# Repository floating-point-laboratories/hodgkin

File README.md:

# Project Hodgkin
Project Hodgkin is an open-source (semi) Arduino Nano compatible microcontroller development board that is developed to IEC 60601 standards for 2xMOPP (methods of patient protection) isolation. It is intended for educational settings to enable students and enthusiasts to safely interface with biopotential amplifier circuits.

**Will this device be IEC 60601 certified / FDA cleared / etc.?**
*Due to the nature of this device's application, which is to enable students to interface with biomedical electronics which they have designed and built themselves, it is not practical to pursue any form of formal medical device certification. This device's performance will depend entirely on the quality of the circuits that it is attached to; it therefore cannot and should not be used as a substitute for any medical device for diagnostic or therapeutic purposes. The intention of this project is to provide a safe interface between these experimental circuits and a computer via USB interface so that users are not exposed to dangerous voltages or currents in the case of PC power supply failure or mains power surge.*

**What do you mean "semi" Arduino Nano compatible?**
*This device is planned to share a pinout, footprint, and firmware with the Arduino Nano V3.0 (based on the ATmega328p microcontroller). However, some changes will be necessary to ensure safe operation of the device while maintaining low cost. These include the inability to draw microcontroller power from the on-board USB port, and incompatibility with shields / expansion boards which are connected to mains power.*

**Why use an optical link? Why not use a wireless connection like BLE?**
*This is something that was certainly considered, but was ultimately abandoned in favor of a direct optical serial link for three primary reasons:*

*1. Cost. The goal for this project is to meet the necessary safety requirements without dramatically adding to the cost of an Arduino Nano. Obviously some added costs are unavoidable, but a full RF solution was deemed an uneccessary cost.*

*2. Stability. Since this project is intended as a direct Aduino Nano substitute for use by students, it was important to us that it behave as similarly to a stock Arduino as possible. This means plug-and-play direct USB-to-serial simplicity whenever possible.*

*3. Security. Athough this device is not intended for use as a medical device, it is built with similar design philosophies in mind. In general, wireless solutions are typically not implemented in medical devices unless there is a compelling reason to do so to avoid potential data leaks / HIPAA violations.*

**When can I purchase this device?**
*This device is planned for inclusion in the electronics kit given to all students enrolled in SBEE 2020. Standalone sale of the device will certainly be considered if there is a demand for it. In the meantime, you are welcome to build one yourself using the files available in this repository.*

## About The Shoulders of Giants
In 1676, Isaac Newton, one of the most influential mathematicians and scientists of all time, famously wrote:

> "If I have seen further, it is by standing on the shoulders of giants."

The Shoulders of Giants, Inc. (TSoG) is a nonprofit (501(c)(3)) organization founded in 2013 on a vision that world-class science education should be available to all students of all ages. Since 2015, The Shoulders of Giants has offered an immersive, ongoing mentorship program for dedicated students who would like the opportunity to study more closely under the guidance of Dr. Steven J. Foland. This program is designed to provide middle and high school students with a broad foundation of knowledge and skills across science and engineering disciplines, experience working and communicating in a professional environment, and helps them develop the study habits necessary to achieve success at the university level and beyond.

In 2019, this world-class program became available to students everywhere with the launch of TSoG.tv. This online platform, created in collaboration between The Shoulders of Giants, Inc. and its sister-company Floating Point Laboratories, LLC, provides at-home exercises, live-streaming, and project support to students anywhere in the world.

## About #SBEE2020
Since 2015, The Shoulders of Giants has offered its flagship summer program, the Summer Biomedical Engineering Experience (SBEE) to high school students interested in exploring careers in biomedical engineering and related medical sciences. The original contents of the program were 60 hours of rigorous curriculum covering biomedical electronics, mechanical CAD and 3D printing, and microcontroller programming. Through this program, nearly 400 students have designed and built their own electromyograph (EMG) controlled prosthetic hands. 

In spring 2019, TSoG co-founder and Floating Point Laboratories managing director Dr. Steven J. Foland [announced an initiative](https://www.youtube.com/watch?v=rmPsDaRs3cc) to develop the SBEE curriculum into a TSoG.tv experience for students around the world in summer 2020. This has become known as the #SBEE2020 initiative. Dr. Foland hosted a successful 24-hour livestream fundraiser on June 29-30th 2019, teaching a prototype SBEE 2020 curriculum in one marathon session which can be viewed [here](https://www.tsogiants.org/2019/07/02/24-hour-challenge-physiological-signals-and-biomedical-electronics/). 

As of August 2019, development for SBEE 2020 is currently underway. In order to best serve the community, several new devices need to be developed to provide safe, affordable access to the technologies necessary for students to explore and interface with human biosignals. Among these are: Project Hodgkin, an inexpensive Arduino compatible microcontroller development board built to follow IEC 60601 safety standards; and Project Huxley, a USB oscilloscope developed with biomedical applications and safety standards in mind.

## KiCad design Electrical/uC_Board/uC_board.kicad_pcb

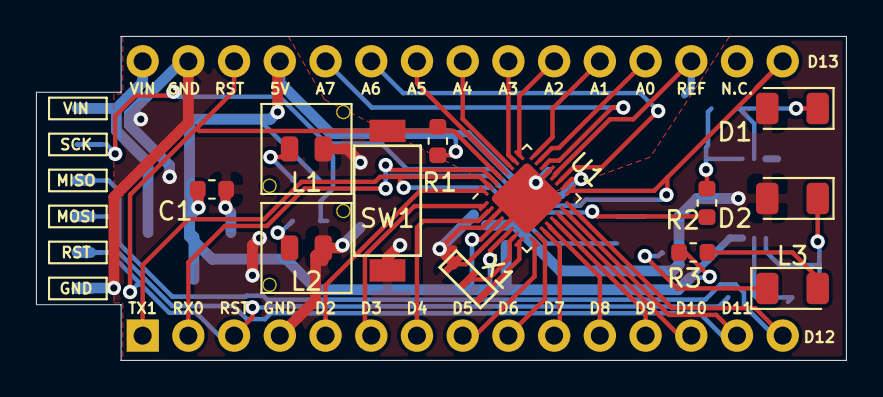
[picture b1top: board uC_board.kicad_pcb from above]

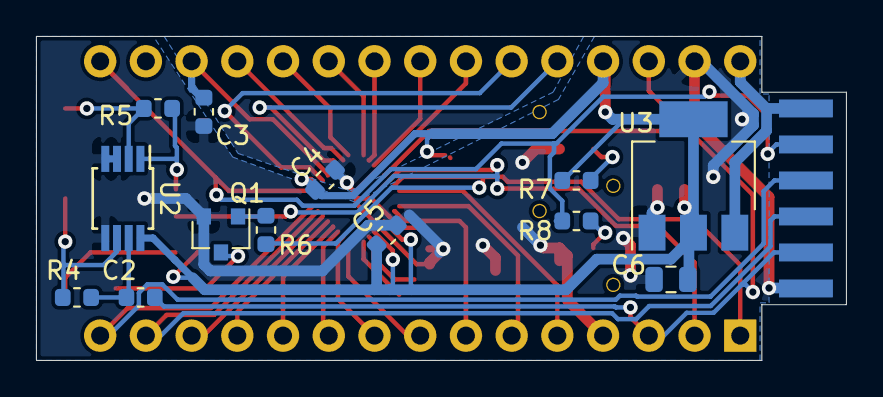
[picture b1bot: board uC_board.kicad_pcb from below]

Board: 2 copper layers, 45.0 x 18.0 mm, 27 parts (14 on the bottom side), 38 nets.

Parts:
C1, C4, C5: 1uF; C_0603_1608Metric
C2, C3: 100nF; C_0603_1608Metric
C6: 4.7uF; C_0805_2012Metric
D1, D2: D_Photo; D_1206_3216Metric
J1: Card Edge Connector; card_edge_6p_single_side
J2: Arduino Breakout Pins; ArdNanoStrip
L1: GREEN; LED_0805_LightPipe_Long
L2: YELLOW; LED_0805_LightPipe_Long
L3: LED; LED_1206_3216Metric
Q1: BC850; SOT-23
R1, R2, R3, R6, R7, R8: 1k; R_0603_1608Metric
R4, R5: 1M; R_0603_1608Metric
SW1: SW_Push; PTS636-G-2.5-NoGND
U1: ATmega328PB-AU; QFN-32-1EP_4x4mm_P0.4mm_EP2.9x2.9mm
U2: OPA2381; MSOP-8_3x3mm_P0.65mm
U3: LM1117MPX-5.0; LM1117
X1: CSTNE16M0V530000R0

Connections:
+5V: C1.1, C4.1, C5.1, C6.1, J2.27, R1.1, R3.2, R7.2, U1.4, U1.6, U1.18, U2.8, U3.2
/A0: J2.19, U1.23
/A1: J2.20, U1.24
/A2: J2.21, U1.25
/A3: J2.22, U1.26
/A4: J2.23, U1.27
/A5: J2.24, U1.28
/A6: J2.25, U1.19
/A7: J2.26, U1.22
/AREF: C3.1, J2.18, U1.20
/D0: J2.2, R2.2, U1.30
/D1: J2.1, R6.2, U1.31
/D2: J2.5, U1.32
/D3: J2.6, U1.1
/D4: J2.7, U1.2
/D5: J2.8, U1.9
/D6: J2.9, U1.10
/D7: J2.10, U1.11
/D8: J2.11, U1.12
/D9: J2.12, U1.13
/D10: J2.13, U1.14
/D11: J1.4, J2.14, U1.15
/D12: J1.3, J2.15, U1.16
/D13: J1.2, J2.16, R8.2, U1.17
/RESET: C2.2, J1.5, J2.3, J2.28, R1.2, SW1.2, U1.29
/RX: R2.1, R5.1, U2.1
/TX: Q1.1, R6.1
GND: C1.2, C3.2, C4.2, C5.2, C6.2, D1.2, D2.2, J1.6, J2.4, J2.29, L1.1, L2.1, Q1.2, SW1.1, U1.3, U1.5, U1.21, U1.33, U2.3, U2.4, U2.5, U3.1, X1.3
unnamed: C2.1, R4.1, U2.7
unnamed: D1.1, R5.2, U2.2
unnamed: D2.1, R4.2, U2.6
unnamed: L1.2, R7.1
unnamed: L2.2, R8.1
unnamed: L3.1, Q1.3
unnamed: L3.2, R3.1
unnamed: U1.7, X1.2
unnamed: U1.8, X1.1
VCC: J1.1, J2.30, U3.3

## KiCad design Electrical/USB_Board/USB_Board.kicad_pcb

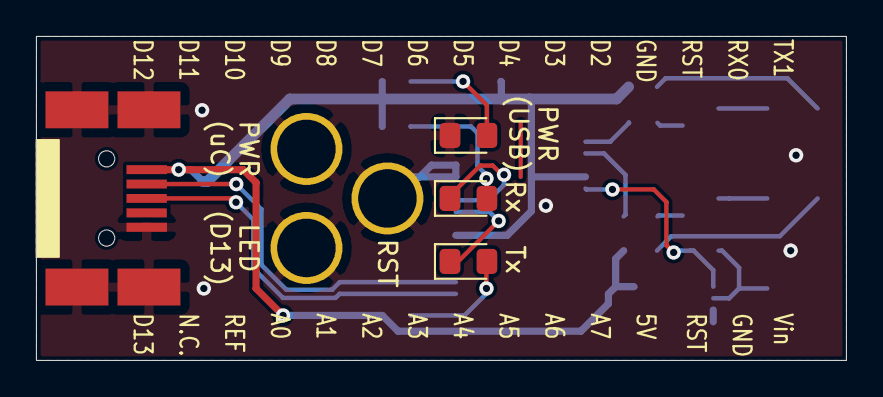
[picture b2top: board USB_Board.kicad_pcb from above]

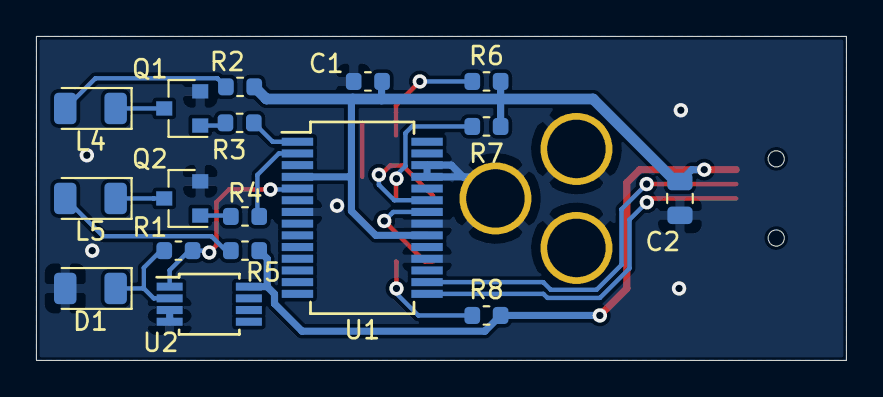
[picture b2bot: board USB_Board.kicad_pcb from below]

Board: 2 copper layers, 45.0 x 18.0 mm, 24 parts (17 on the bottom side), 19 nets.

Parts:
C1: 100 nF; C_0603_1608Metric
C2: 4.7uF; C_0805_2012Metric
D1: PD_RX; D_1206_3216Metric
H1, H2: light_pipe
H3: Switch; light_pipe
J1: USB_B_Mini; Molex_67503-1020
L1: blue; LED_0805_2012Metric_Pad1.15x1.40mm_HandSolder
L2: red; LED_0805_2012Metric_Pad1.15x1.40mm_HandSolder
L3: green; LED_0805_2012Metric_Pad1.15x1.40mm_HandSolder
L4: IR_TX; LED_1206_3216Metric
L5: IR_DTR; LED_1206_3216Metric
Q1, Q2: BC850; SOT-23
R1, R2, R5, R7, R8: R; R_0603_1608Metric
R3, R4: 4.7k; R_0603_1608Metric
R6: R_US; R_0603_1608Metric
U1: FT232RL; SSOP-28_5.3x10.2mm_P0.65mm
U2: OPA2381; MSOP-8_3x3mm_P0.65mm

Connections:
+5V: C1.1, C2.1, J1.1, R2.2, R5.2, R6.2, R7.2, R8.2, U1.4, U1.20, U2.8
/DTR: R4.1, U1.2
GND: C1.2, C2.2, D1.2, H1.1, H2.1, H3.1, J1.5, J1.6, L1.1, Q1.2, Q2.2, U1.7, U1.18, U1.21, U1.25, U1.26, U2.3, U2.4
unnamed: D1.1, R1.2, U2.2
unnamed: J1.2, U1.16
unnamed: J1.3, U1.15
unnamed: L1.2, R6.1
unnamed: L2.1, U1.23
unnamed: L2.2, R7.1
unnamed: L3.1, U1.22
unnamed: L3.2, R8.1
unnamed: L4.1, Q1.3
unnamed: L4.2, R2.1
unnamed: L5.1, Q2.3
unnamed: L5.2, R5.1
unnamed: Q1.1, R3.2
unnamed: Q2.1, R4.2
unnamed: R1.1, U1.5, U2.1
unnamed: R3.1, U1.1

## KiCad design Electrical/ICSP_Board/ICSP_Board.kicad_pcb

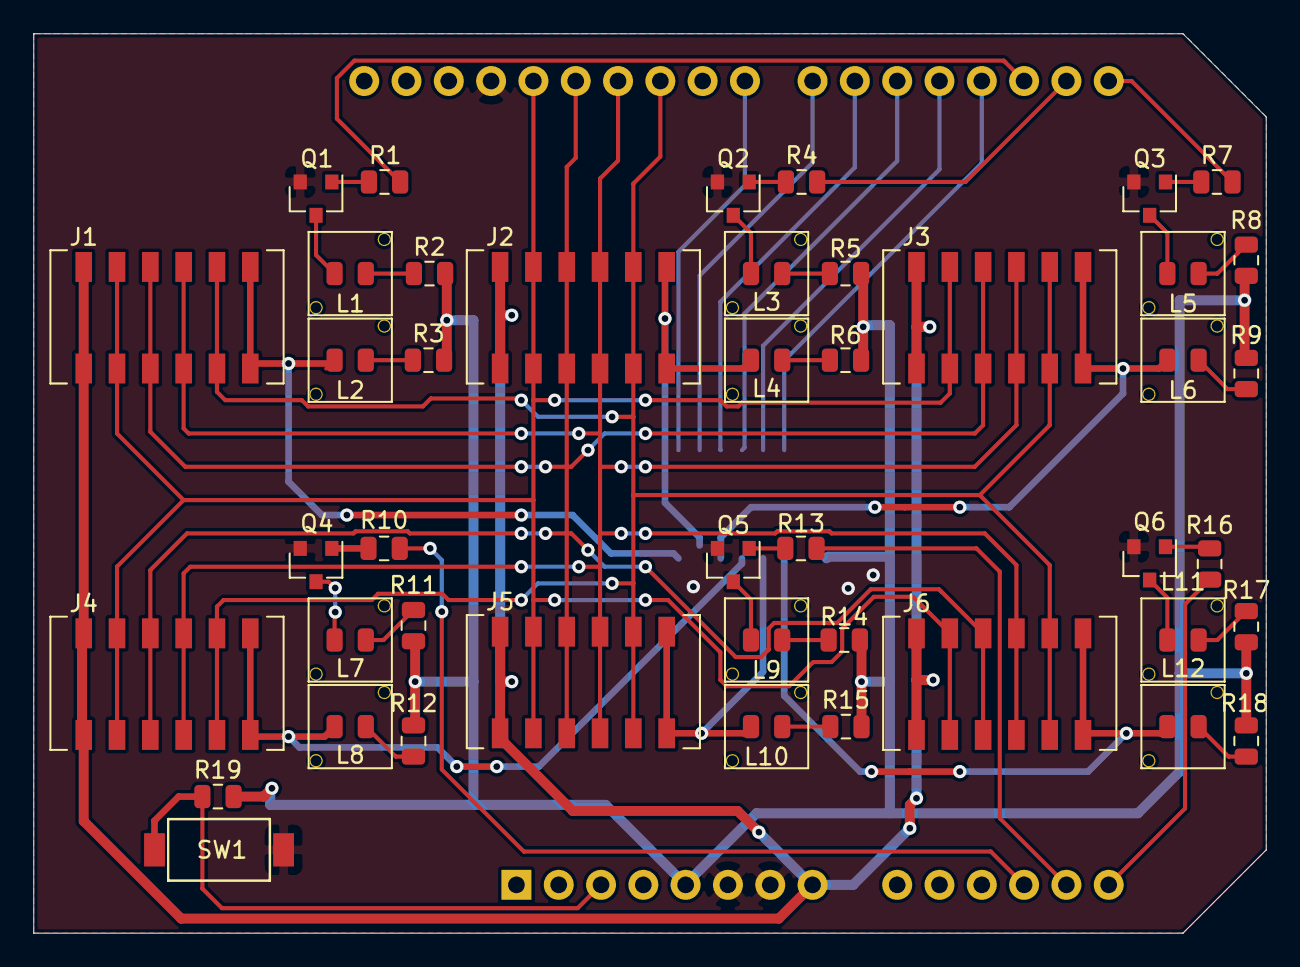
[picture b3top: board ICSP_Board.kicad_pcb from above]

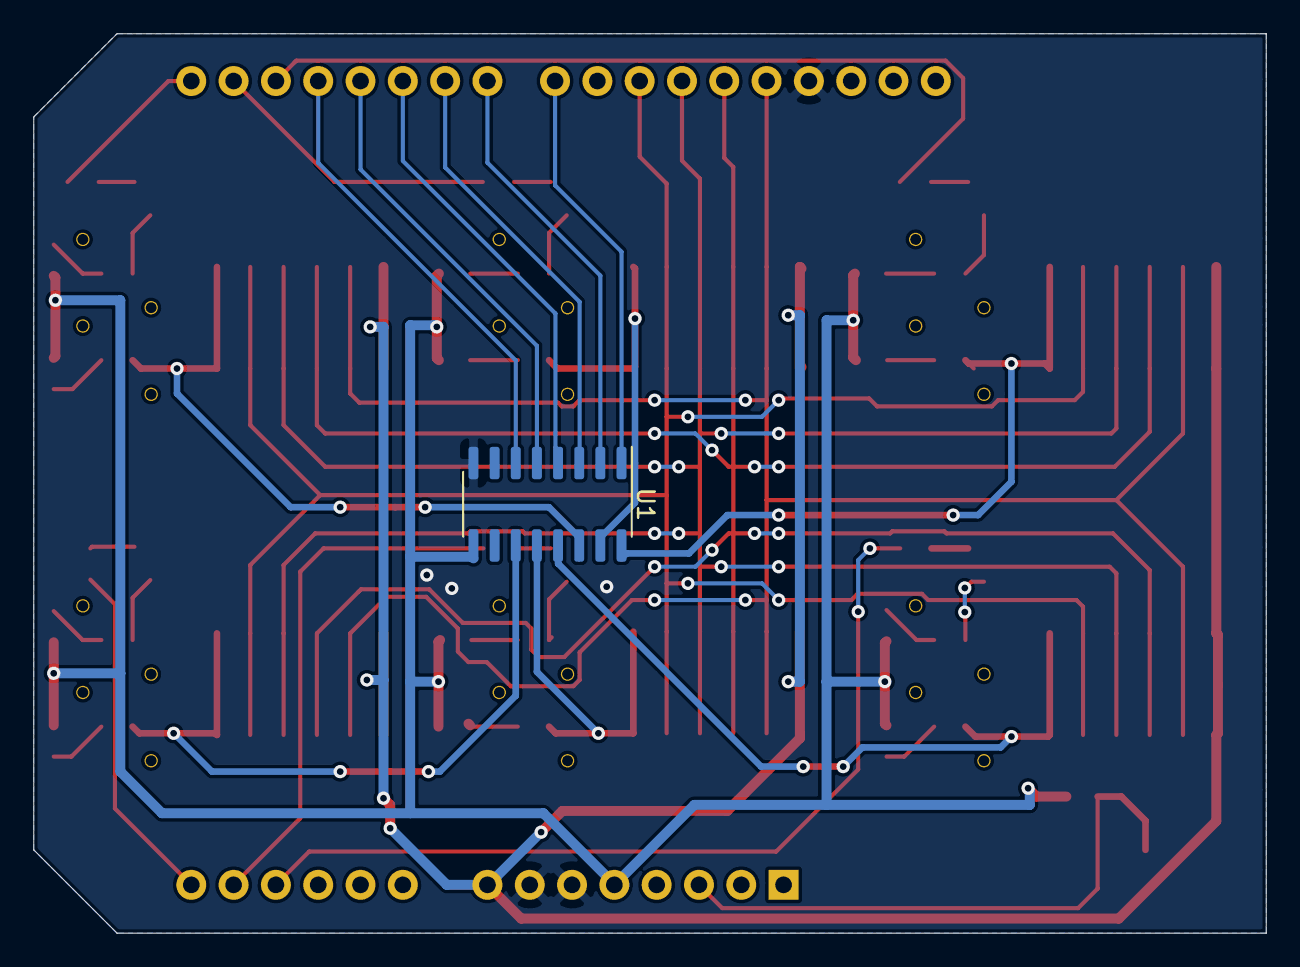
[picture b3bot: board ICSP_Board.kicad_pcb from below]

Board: 2 copper layers, 74.0 x 54.0 mm, 46 parts (2 on the bottom side), 50 nets.

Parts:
A1: Arduino_UNO_R3
J1, J2, J3, J4, J5, J6: AVX 009159006551906; card_edge_6p
L1, L3, L5, L7, L9, L11: gLED; LED_0805_LightPipe
L2, L4, L6, L8, L10, L12: rLED; LED_0805_LightPipe
Q1, Q2, Q3, Q4, Q5, Q6: BC850; SOT-23
R1, R2, R3, R4, R5, R6, R7, R8, R9, R10, R11, R12, R13, R14, R15, R16, R17, R18, R19: R_US; R_0805_2012Metric
SW1: SW_Push; PTS636-G-2.5-NoGND
U1: ULN2003A; SOIC-16_3.9x9.9mm_P1.27mm

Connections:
+5V: A1.5, R2.1, R3.1, R5.1, R6.1, R8.1, R9.1, R11.1, R12.1, R14.1, R15.1, R17.1, R18.1, R19.1, U1.9
/G1: L1.1, Q1.3
/G2: L3.1, Q2.3
/G3: L5.1, Q3.3
/G4: L7.1, Q4.3
/G5: L9.1, Q5.3
/G6: L11.1, Q6.3
/MISO: A1.27, J1.3, J2.3, J3.3, J4.3, J5.3, J6.3
/MOSI: A1.26, J1.4, J2.4, J3.4, J4.4, J5.4, J6.4
/RST: A1.25, J1.5, J2.5, J3.5, J4.5, J5.5, J6.5
/SCK: A1.28, J1.2, J2.2, J3.2, J4.2, J5.2, J6.2
/SW1: A1.3, R19.2, SW1.2
/ULN11: J6.6, L12.1, U1.11
/ULN12: J5.6, L10.1, U1.12
/ULN13: J4.6, L8.1, U1.13
/ULN14: J3.6, L6.1, U1.14
/ULN15: J2.6, L4.1, U1.15
/ULN16: J1.6, L2.1, U1.16
GND: A1.6, A1.7, A1.29, Q1.2, Q2.2, Q3.2, Q4.2, Q5.2, Q6.2, SW1.1, U1.8
unnamed: A1.12, R10.1
unnamed: A1.13, R13.1
unnamed: A1.14, R16.1
unnamed: A1.15, R7.1
unnamed: A1.16, R4.1
unnamed: A1.17, R1.1
unnamed: A1.18, U1.6
unnamed: A1.19, U1.5
unnamed: A1.20, U1.4
unnamed: A1.21, U1.3
unnamed: A1.22, U1.2
unnamed: A1.23, U1.1
unnamed: L1.2, R2.2
unnamed: L2.2, R3.2
unnamed: L3.2, R5.2
unnamed: L4.2, R6.2
unnamed: L5.2, R8.2
unnamed: L6.2, R9.2
unnamed: L7.2, R11.2
unnamed: L8.2, R12.2
unnamed: L9.2, R14.2
unnamed: L10.2, R15.2
unnamed: L11.2, R17.2
unnamed: L12.2, R18.2
unnamed: Q1.1, R1.2
unnamed: Q2.1, R4.2
unnamed: Q3.1, R7.2
unnamed: Q4.1, R10.2
unnamed: Q5.1, R13.2
unnamed: Q6.1, R16.2
VCC: A1.8, J1.1, J2.1, J3.1, J4.1, J5.1, J6.1

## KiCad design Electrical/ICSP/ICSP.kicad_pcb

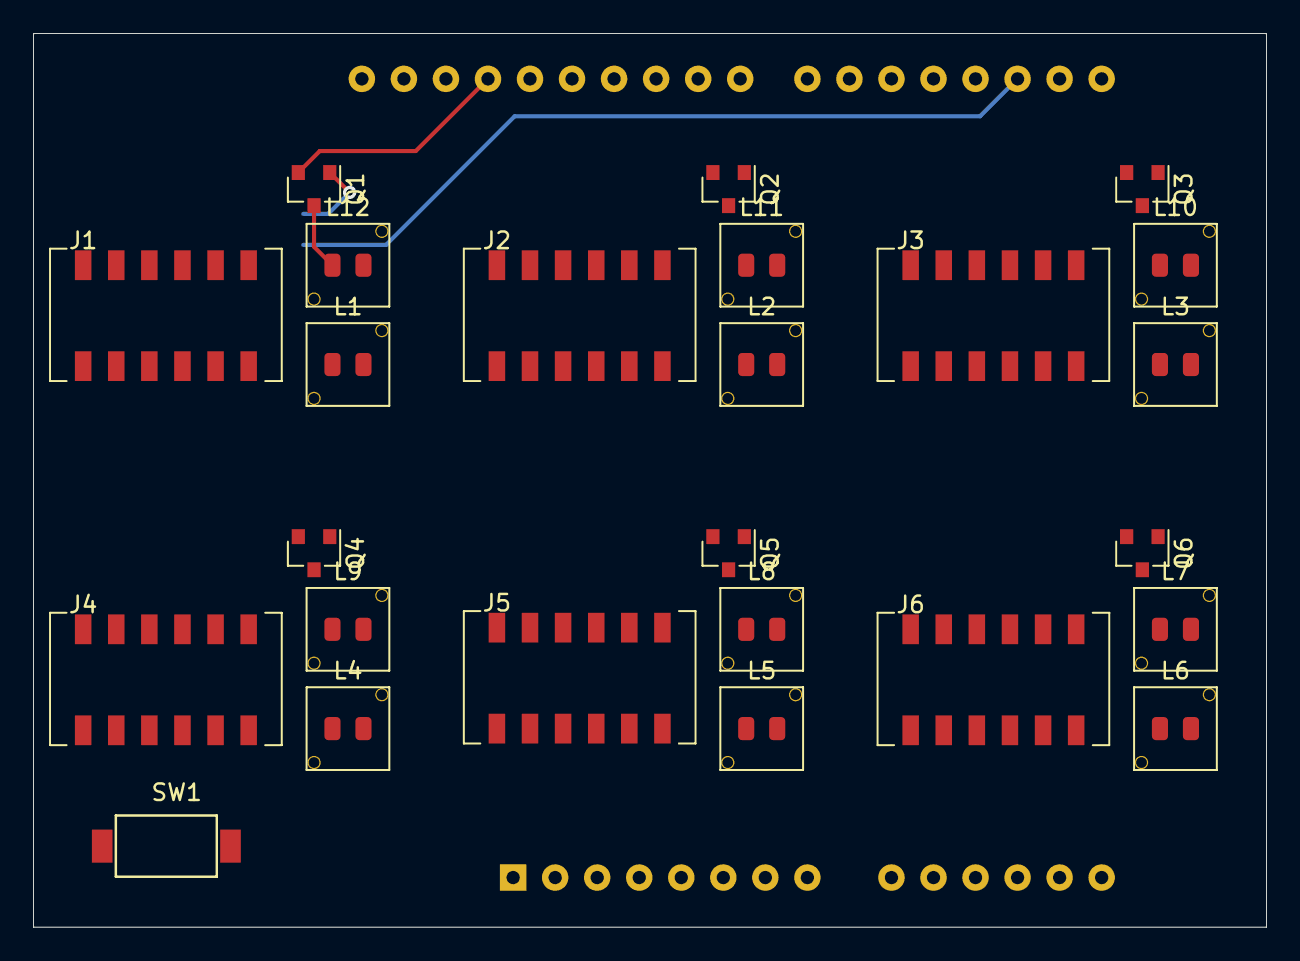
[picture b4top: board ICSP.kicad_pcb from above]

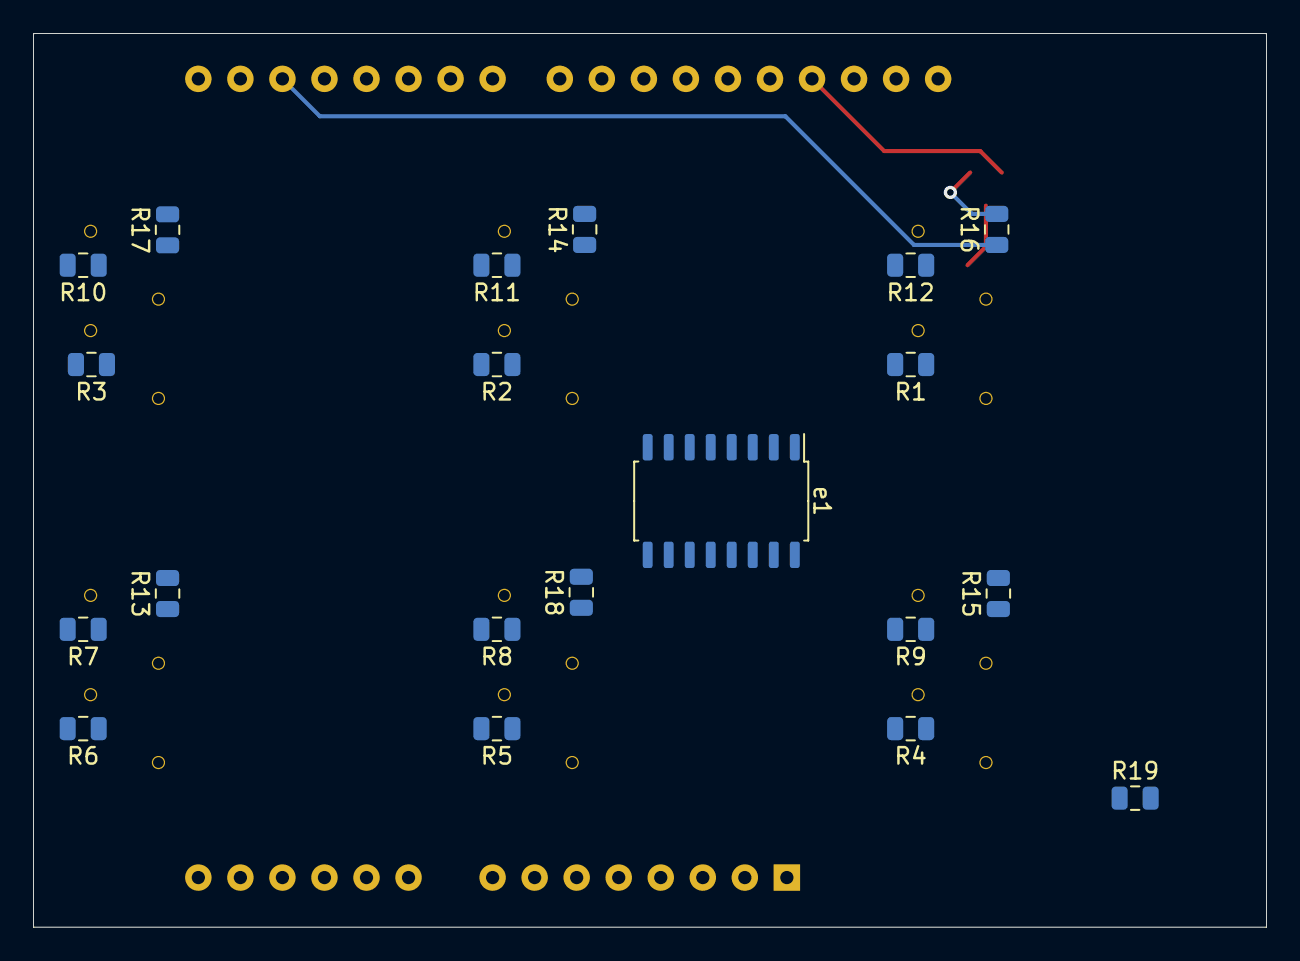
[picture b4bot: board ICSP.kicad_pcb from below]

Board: 2 copper layers, 74.5 x 54.0 mm, 46 parts (21 on the bottom side), 49 nets.

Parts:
A1: Arduino_UNO_R3
J1, J2, J3, J4, J5, J6: card_edge_6p
L1, L2, L3, L4, L5, L6: rLED; LED_0805_LightPipe
L7, L8, L9, L10, L11, L12: gLED; LED_0805_LightPipe
Q1, Q2, Q3, Q4, Q5, Q6: BC850; SOT-23
R1, R2, R3, R4, R5, R6, R7, R8, R9, R10, R11, R12, R13, R14, R15, R16, R17, R18, R19: R_US; R_0805_2012Metric
SW1: SW_Push; PTS636-G-2.5-NoGND
e1: ULN2003A; SOP-16_4.55x10.3mm_P1.27mm

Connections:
+5V: A1.5, J1.1, J2.1, J3.1, J4.1, J5.1, J6.1, R1.1, R2.1, R3.1, R4.1, R5.1, R6.1, R7.1, R8.1, R9.1, R10.1, R11.1, R12.1, R19.1, e1.9
/G1: L12.1, Q1.3
/G2: L11.1, Q2.3
/G3: L10.1, Q3.3
/G4: L9.1, Q4.3
/G5: L8.1, Q5.3
/G6: L7.1, Q6.3
/MISO: A1.27, J1.3, J2.3, J3.3, J4.3, J5.3, J6.3
/MOSI: A1.26, J1.4, J2.4, J3.4, J4.4, J5.4, J6.4
/RST: A1.25, J1.5, J2.5, J3.5, J4.5, J5.5, J6.5
/SCK: A1.28, J1.2, J2.2, J3.2, J4.2, J5.2, J6.2
/SW1: A1.3, R19.2, SW1.2
/ULN11: J6.6, L6.1, e1.11
/ULN12: J5.6, L5.1, e1.12
/ULN13: J4.6, L4.1, e1.13
/ULN14: J3.6, L3.1, e1.14
/ULN15: J2.6, L2.1, e1.15
/ULN16: J1.6, L1.1, e1.16
GND: A1.6, A1.7, A1.29, Q1.2, Q2.2, Q3.2, Q4.2, Q5.2, Q6.2, SW1.1, e1.8
unnamed: A1.12, R15.1
unnamed: A1.13, R18.1
unnamed: A1.14, R13.1
unnamed: A1.15, R17.1
unnamed: A1.16, R14.1
unnamed: A1.17, R16.1
unnamed: A1.18, e1.6
unnamed: A1.19, e1.5
unnamed: A1.20, e1.4
unnamed: A1.21, e1.3
unnamed: A1.22, e1.2
unnamed: A1.23, e1.1
unnamed: L1.2, R1.2
unnamed: L2.2, R2.2
unnamed: L3.2, R3.2
unnamed: L4.2, R4.2
unnamed: L5.2, R5.2
unnamed: L6.2, R6.2
unnamed: L7.2, R7.2
unnamed: L8.2, R8.2
unnamed: L9.2, R9.2
unnamed: L10.2, R10.2
unnamed: L11.2, R11.2
unnamed: L12.2, R12.2
unnamed: Q1.1, R16.2
unnamed: Q2.1, R14.2
unnamed: Q3.1, R17.2
unnamed: Q4.1, R15.2
unnamed: Q5.1, R18.2
unnamed: Q6.1, R13.2

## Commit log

2019-08-10 Created libraries.
2019-08-10 added usb port, and ft232RL to PCB
2019-08-10 started board 2, made a few new parts
2019-08-10 Update USB_Board_1.sch
    made the sch cleaner
2019-08-10 Added transimpedance amp opa2381
2019-08-10 added 3.3v regulator
2019-08-10 Update USB_Board_1.sch
    added symbols for led and photodiodes: no footprints selected
2019-08-10 Added BOM for ICSP board.
2019-08-10 Update Bom.csv with FT232RL and MF-MSMF 050
2019-08-10 updated footprint for led
2019-08-10 assigned footprints and began creating footprint for oscillator
2019-08-10 End of Saturday stream.
2019-08-11 updated the footprint for the fuse.
2019-08-11 Restructured repository.
2019-08-11 fixed symbol issue
2019-08-11 added reset leds, relabeled schmatic symbols for readablitiy.
2019-08-11 added ICSP, need to add LED and PD
2019-08-11 added BOMs for uC and USB board
2019-08-11 fixed transimpedence_photodiode connection on schematic
2019-08-11 added atmega footprint, started PCB
2019-08-11 assigned footprints to schematic
2019-08-11 Updated ICSP board.
2019-08-11 Finalized initial ICSP board layout.
2019-08-11 started pcb layout
2019-08-11 forgot to save before pushing
2019-08-12 Minor arduino nano footprint modifications.
2019-08-12 Updated schematic symbols.
2019-08-12 changed 3.3v regulator to 5v regulator, laid things out on pcb
2019-08-12 Completed r1 of USB Board.
2019-08-12 changed sizes of resistors and capacitors, trying to neatly lay things out on pcb
2019-08-12 Added light pipe package.
2019-08-12 trying to do stuff idk
2019-08-12 Updated LED locations on USB Board.
2019-08-12 locking in LED and PDs
2019-08-12 forgot to save earlier
2019-08-12 Updated uC board cuts and card edge contacts.
2019-08-13 stuff
2019-08-13 updated BOM
2019-08-13 fixed tx connection to have transistor. gave myself a headache trying to figure out a good place to put the atmega
2019-08-15 Assisted with uC board component placement.
2019-08-15 Finished draft of USB board.
2019-08-15 adding traces, removed auto selector, changed diode footprints
2019-08-15 i have no idea where these last traces are supposed to go
2019-08-15 Fixed layout for USB board.
2019-08-15 Added QFN-32 to hodgkin footprint library.
2019-08-15 forgot a file
2019-08-15 changed atmega, started re-laying traces
2019-08-15 Update fp-info-cache
2019-08-17 finished first try of traces, problems with GND plane
2019-08-17 Finalized USB Board, inc. 3D models of light pipes.
2019-08-17 Deleted fuse from libraries because it is no longer in use.
2019-08-17 Finished draft of uC Board. Need to add 3D packages.
2019-08-19 Fixed part numbers on USB board.
2019-08-19 changed LED and PD footprints on USB boards
2019-08-19 Fixed footprints on uC board.
2019-08-19 Fixed minor ground plane issues on uC Board.
2019-08-19 Added header pins to uC board 3D model.
2019-08-19 Cleaned up folders for USB and ICSP boards.
2019-08-21 Began exstablishing files for Mechanical design.
2019-08-21 Prepared electrical models for mechanical assembly in FreeCAD.
2019-08-22 Fixed hole size on ICSP board.
2019-08-22 Initial ICSP housing rough cut.
2019-10-03 Created Housing Top for ICSP in FreeCAD (again).
2019-10-03 Completed upper-housing for ICSP.
2019-10-10 Began Hodgkin housing parts.
2019-10-17 Updated BOMs.
2019-10-17 Updated transimpedance amp and rearranged USB board.
2019-10-17 Remade the mechanical assemblies for the Hodgkin boards.
2019-10-26 Finalized Housing.
